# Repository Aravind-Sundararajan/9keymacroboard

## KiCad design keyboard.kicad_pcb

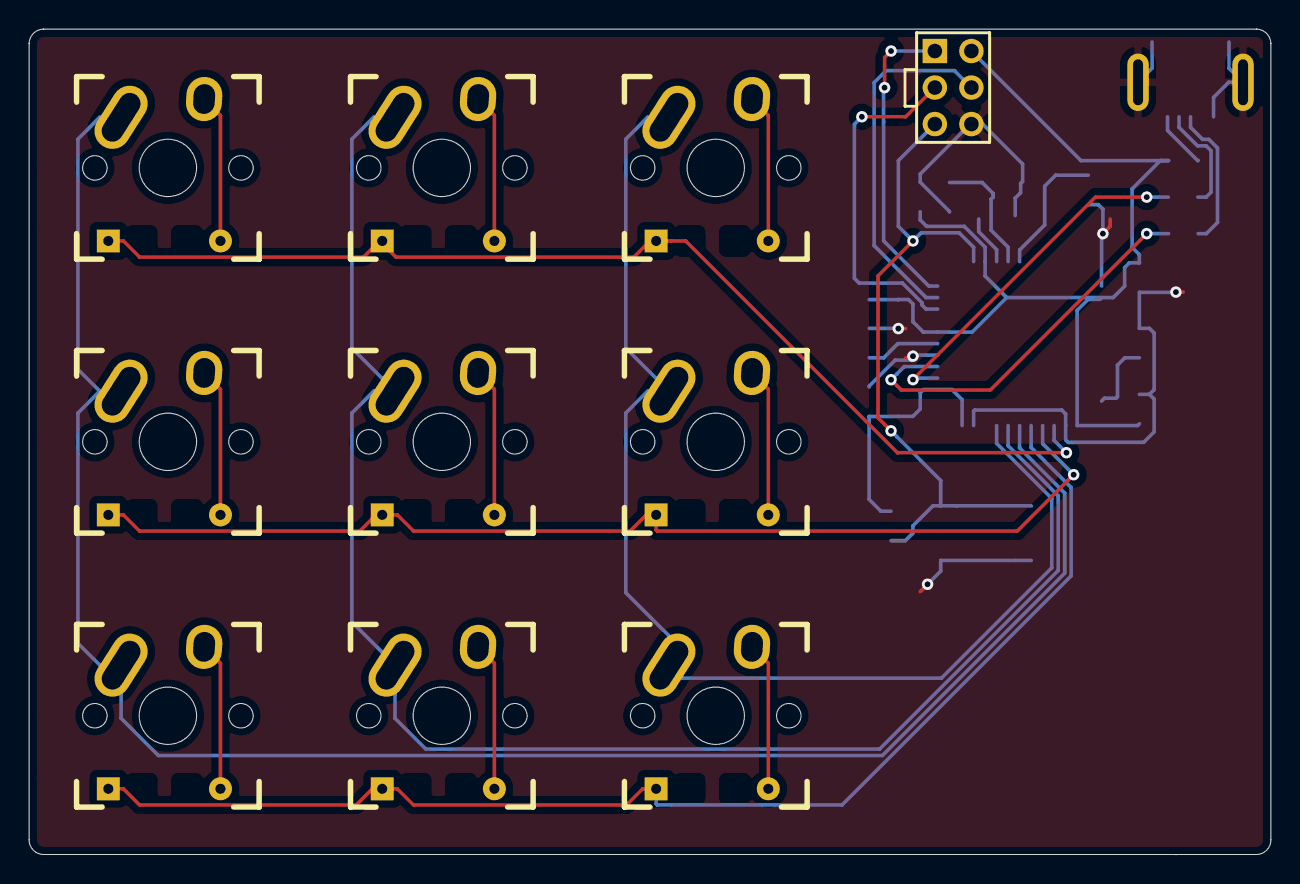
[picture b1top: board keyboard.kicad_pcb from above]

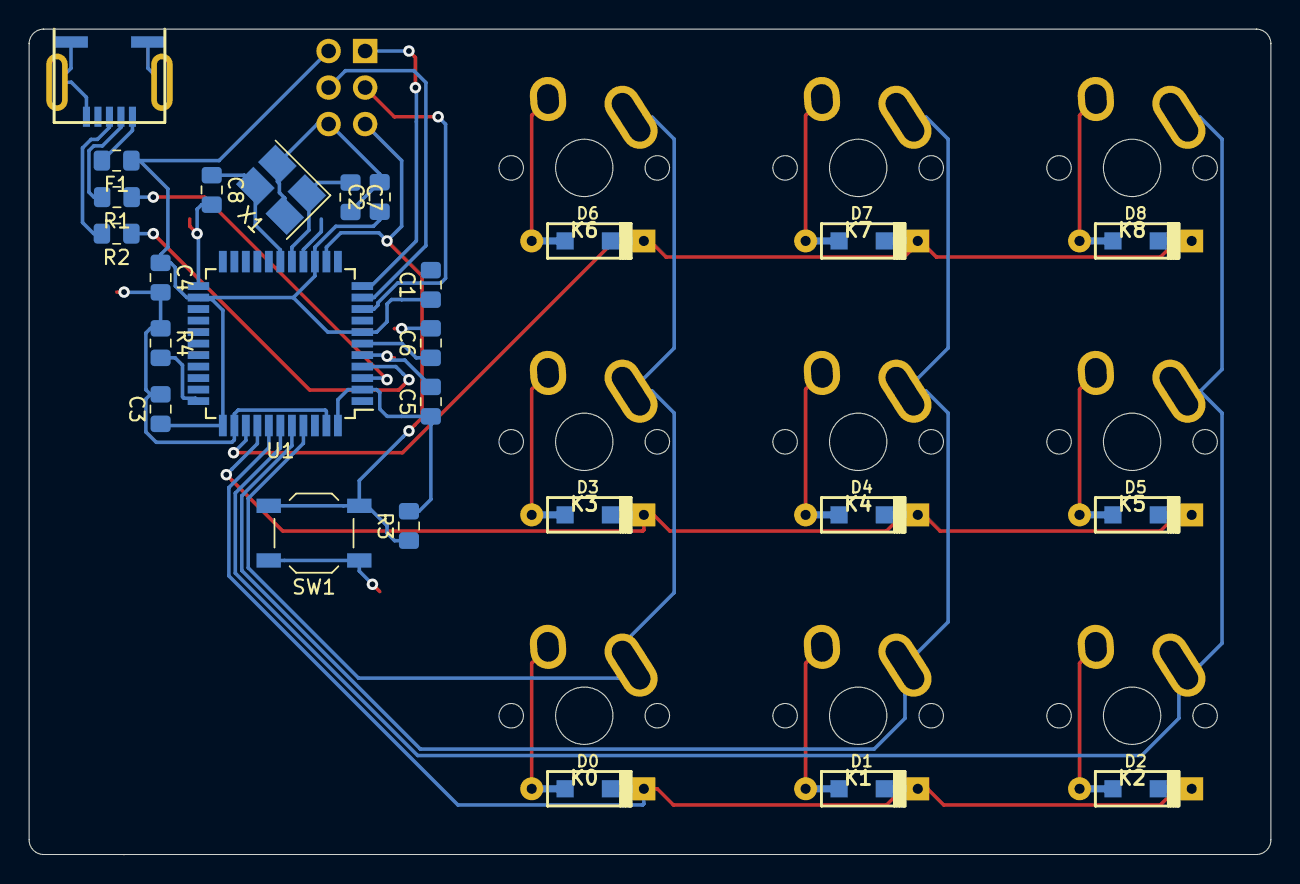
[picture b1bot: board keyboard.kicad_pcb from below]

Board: 2 copper layers, 86.4 x 57.4 mm, 36 parts (26 on the bottom side), 30 nets.

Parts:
C1, C2, C3, C4: 0.1u; C_0805_2012Metric_Pad1.15x1.40mm_HandSolder
C5: 4.7u; C_0805_2012Metric_Pad1.15x1.40mm_HandSolder
C6: 1u; C_0805_2012Metric_Pad1.15x1.40mm_HandSolder
C7, C8: 22p; C_0805_2012Metric_Pad1.15x1.40mm_HandSolder
D0, D1, D2, D3, D4, D5, D6, D7, D8: D; D_SOD123_axial
F1: Polyfuse; Fuse_0805_2012Metric_Pad1.15x1.40mm_HandSolder
J1: USB_mini_micro_B; USB_miniB_hirose_5S8
J2: AVR-ISP-6; AVR_ICSP_3x2
K0, K1, K2, K3, K4, K5, K6, K7, K8: KEYSW; Mx_Alps_100
R1, R2: 22; R_0805_2012Metric_Pad1.15x1.40mm_HandSolder
R3, R4: 10k; R_0805_2012Metric_Pad1.15x1.40mm_HandSolder
SW1: SW_PUSH; SW_SPST_TL3342
U1: ATMEGA32U4; TQFP-44_10x10mm_P0.8mm
X1: XTAL_GND; Crystal_SMD_SeikoEpson_TSX3225-4Pin_3.2x2.5mm_HandSoldering

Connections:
/avrisp/miso: J2.1, U1.11
/avrisp/mosi: J2.4, U1.10
/avrisp/sck: J2.3, U1.9
/resetSwitch/reset: J2.5, R3.1, SW1.2, U1.13
/xtalgnd/xtal1: C7.1, U1.16, X1.1
/xtalgnd/xtal2: C8.1, U1.17, X1.3
GND: C1.2, C2.2, C3.2, C4.2, C5.2, C6.2, C7.2, C8.2, J1.5, J1.6, J2.6, R4.1, SW1.1, U1.5, U1.15, U1.23, U1.35, U1.43, X1.2, X1.4
Mcol0: K0.1, K3.1, K6.1, U1.41
Mcol1: K1.1, K4.1, K7.1, U1.40
Mcol2: K2.1, K5.1, K8.1, U1.39
Mrow0: D0.1, D1.1, D2.1, U1.38
Mrow1: D3.1, D4.1, D5.1, U1.37
Mrow2: D6.1, D7.1, D8.1, U1.36
unnamed: C6.1, U1.6
unnamed: D0.2, K0.2
unnamed: D1.2, K1.2
unnamed: D2.2, K2.2
unnamed: D3.2, K3.2
unnamed: D4.2, K4.2
unnamed: D5.2, K5.2
unnamed: D6.2, K6.2
unnamed: D7.2, K7.2
unnamed: D8.2, K8.2
unnamed: F1.2, J1.1
unnamed: J1.2, R1.2
unnamed: J1.3, R2.2
unnamed: R1.1, U1.3
unnamed: R2.1, U1.4
unnamed: R4.2, U1.33
VCC: C1.1, C2.1, C3.1, C4.1, C5.1, F1.1, J2.2, R3.2, U1.2, U1.7, U1.14, U1.24, U1.34, U1.44

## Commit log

2020-07-23 adding image
